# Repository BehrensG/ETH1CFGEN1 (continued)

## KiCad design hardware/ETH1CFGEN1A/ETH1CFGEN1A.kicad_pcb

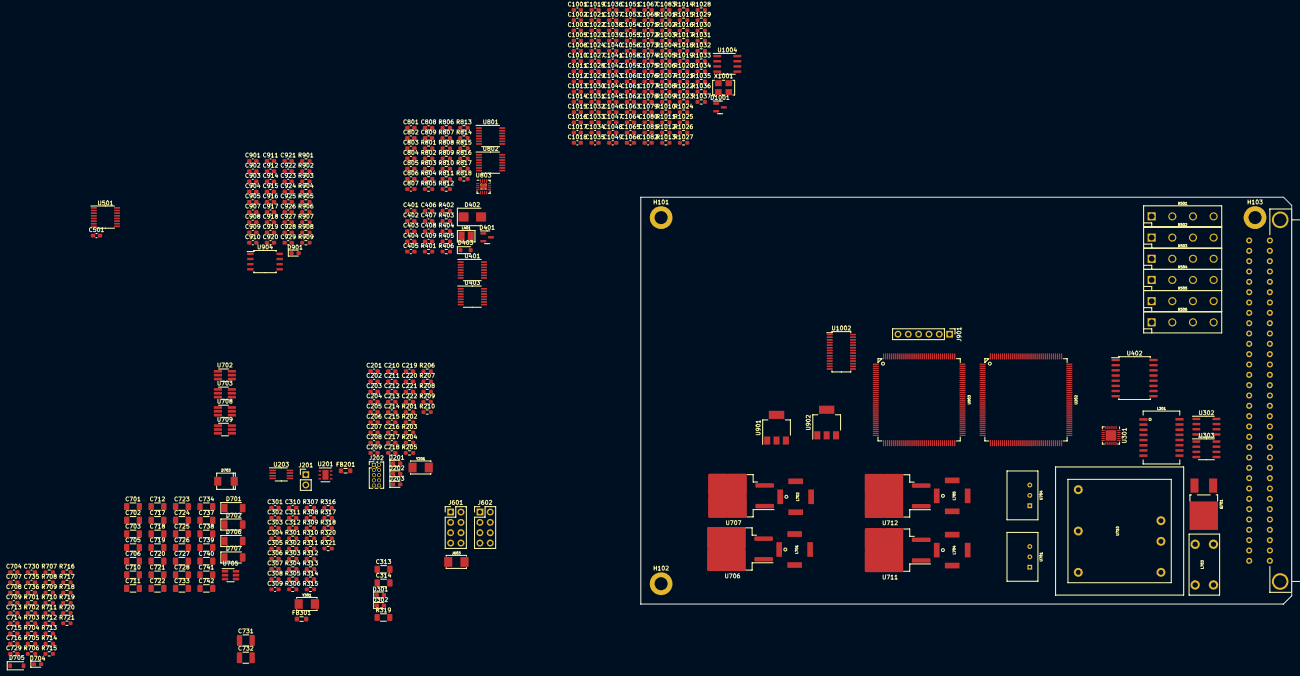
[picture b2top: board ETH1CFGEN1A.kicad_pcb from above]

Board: 4 copper layers, 160.0 x 100.0 mm, 395 parts (1 on the bottom side), 228 nets, no tracks yet.

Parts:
C201, C202, C204, C207, C209, C211, C212, C213, C214, C215, C216, C217, C218, C219, C220, C222, C302, C305, C308, C309, C310, C311, C312, C401, C403, C404, C406, C408, C707, C714, C801, C802, C803, C804, C805, C806, C808, C901, C902, C903, C904, C905, C907, C908, C909, C910, C911, C912, C914, C915, C916, C917, C918, C919, C920, C921, C922, C923, C924, C925, C926, C927, C928, C929, C1003, C1005, C1006, C1012, C1017, C1041, C1044, C1045, C1051, C1065, C1066: 100n; C_0603_1608Metric_Pad1.08x0.95mm_HandSolder
C203, C205, C301, C304: 8p; C_0603_1608Metric_Pad1.08x0.95mm_HandSolder
C206, C208: 2u2; C_0603_1608Metric_Pad1.08x0.95mm_HandSolder
C210, C221, C306, C307, C402, C405, C407, C501, C704, C708, C709, C713, C729, C730, C807, C809: 1u; C_0603_1608Metric_Pad1.08x0.95mm_HandSolder
C303: 470p; C_0603_1608Metric_Pad1.08x0.95mm_HandSolder
C313, C314: 1n/1kV; C_1206_3216Metric_Pad1.33x1.80mm_HandSolder
C409, C1067, C1068, C1080: 47p; C_0603_1608Metric_Pad1.08x0.95mm_HandSolder
C701, C710: 1u/50V; C_1206_3216Metric_Pad1.33x1.80mm_HandSolder
C702, C703, C725, C726: 10u/50V; C_1206_3216Metric_Pad1.33x1.80mm_HandSolder
C705, C706, C717, C718, C719, C720, C723, C724, C727, C728, C739: 4u7/50V; C_1206_3216Metric_Pad1.33x1.80mm_HandSolder
C711, C712, C733, C734: 1u/HC; C_1206_3216Metric_Pad1.33x1.80mm_HandSolder
C715, C716, C735, C736: 4p7; C_0603_1608Metric_Pad1.08x0.95mm_HandSolder
C721, C722: 10u/35V; C_1206_3216Metric_Pad1.33x1.80mm_HandSolder
C731, C732: 330p/2kV; C_1210_3225Metric_Pad1.33x2.70mm_HandSolder
C737, C738, C740: 4u7/25V; C_1206_3216Metric_Pad1.33x1.80mm_HandSolder
C741, C742: 10u/25V; C_1206_3216Metric_Pad1.33x1.80mm_HandSolder
C1001, C1002, C1013, C1014, C1018, C1019, C1031, C1032, C1042, C1043, C1058, C1059, C1082: 33p; C_0603_1608Metric_Pad1.08x0.95mm_HandSolder
C1010, C1011, C1061, C1062, C1075, C1077: 100p; C_0603_1608Metric_Pad1.08x0.95mm_HandSolder
C1015, C1016: 30p; C_0603_1608Metric_Pad1.08x0.95mm_HandSolder
C1021, C1022, C1027, C1028, C1033, C1034, C1055, C1056: 56p; C_0603_1608Metric_Pad1.08x0.95mm_HandSolder
C1023, C1024: 3p3; C_0603_1608Metric_Pad1.08x0.95mm_HandSolder
C1029, C1030: 120p; C_0603_1608Metric_Pad1.08x0.95mm_HandSolder
C1035, C1036, C1083: 150p; C_0603_1608Metric_Pad1.08x0.95mm_HandSolder
C1037, C1038: 62p; C_0603_1608Metric_Pad1.08x0.95mm_HandSolder
C1039, C1040: 8p2; C_0603_1608Metric_Pad1.08x0.95mm_HandSolder
C1046, C1047: 130p; C_0603_1608Metric_Pad1.08x0.95mm_HandSolder
C1048, C1049: 330p; C_0603_1608Metric_Pad1.08x0.95mm_HandSolder
C1053, C1054, C1081: 15p; C_0603_1608Metric_Pad1.08x0.95mm_HandSolder
C1060, C1071: 220n; C_0603_1608Metric_Pad1.08x0.95mm_HandSolder
C1063, C1064: 5p6; C_0603_1608Metric_Pad1.08x0.95mm_HandSolder
C1072, C1073: 22p; C_0603_1608Metric_Pad1.08x0.95mm_HandSolder
C1074, C1078, C1079: 10p; C_0603_1608Metric_Pad1.08x0.95mm_HandSolder
C1076: 1p; C_0603_1608Metric_Pad1.08x0.95mm_HandSolder
D201, D901: BLUE; LED_0603_1608Metric_Pad1.05x0.95mm_HandSolder
D202, D704: RED; LED_0603_1608Metric_Pad1.05x0.95mm_HandSolder
D203, D302: GREEN; LED_0603_1608Metric_Pad1.05x0.95mm_HandSolder
D301: YELLOW; LED_0603_1608Metric_Pad1.05x0.95mm_HandSolder
D401: BAV99; SOT-23
D402: SMBJ5.0A; D_SMB
D403: SD36C-01FTG; D_SOD-323_HandSoldering
D701, D702, D706, D707: PMEG6010EP,115; D_SOD-128
D703: SM6T30AY; DO_214AA_REV
D705: MMSZ5249B; D_SOD-123
D1001: BAS40-04; SOT-23
F701: MF-LSMF185/33X; Fuse_SMD2920
FB201, FB301: 742792031; L_0805_2012Metric_Pad1.05x1.20mm_HandSolder
H101, H102, H103: MountingHole; MountingHole_3.2mm_M3_DIN965_Pad
J201: Conn_02x01; PinHeader_1x02_P2.54mm_Vertical
J202: 20021111-00010T4LF; PinHeader_2x05_P1.27mm_Vertical
J501: C64AC; Socket_DIN41612-CaseC1-AC-Male-64Pin-2rows
J601, J602: Conn_02x04_Odd_Even; PinHeader_2x04_P2.54mm_Vertical
J603: Conn_Coaxial; NX5032GA
J901: Conn_01x06; PinHeader_1x06_P2.54mm_Vertical
K501, K502, K503, K504, K505, K506: HE3621A0510; HE360_x-5050462-8
L301: 749010012A
L401: CW252016-R33G; CW252016
L701, L702, L704, L705: 74489440068
L703: 7448014501
Q701: IRFR5410; TO-252-2_Rectifier
R201, R205: 680; R_0603_1608Metric_Pad0.98x0.95mm_HandSolder
R202, R209, R210, R303, R306, R307, R308, R309, R311, R401, R901, R902, R909, R1002, R1017, R1023, R1027: 10k; R_0603_1608Metric_Pad0.98x0.95mm_HandSolder
R203: 560; R_0603_1608Metric_Pad0.98x0.95mm_HandSolder
R204, R206, R207, R208, R817, R818, R904, R908: 4k7; R_0603_1608Metric_Pad0.98x0.95mm_HandSolder
R301, R302, R304, R305: 33; R_0603_1608Metric_Pad0.98x0.95mm_HandSolder
R310: 1k5; R_0603_1608Metric_Pad0.98x0.95mm_HandSolder
R312: 12k1; R_0603_1608Metric_Pad0.98x0.95mm_HandSolder
R313, R314: 270; R_0603_1608Metric_Pad0.98x0.95mm_HandSolder
R315, R316, R317, R318: 49R9; R_0603_1608Metric_Pad0.98x0.95mm_HandSolder
R319: 1M/1kV; R_1206_3216Metric_Pad1.30x1.75mm_HandSolder
R320, R321: 75/1%; R_0603_1608Metric_Pad0.98x0.95mm_HandSolder
R402: 14k7; R_0603_1608Metric_Pad0.98x0.95mm_HandSolder
R403, R1005, R1015, R1016, R1019, R1022, R1025: 100; R_0603_1608Metric_Pad0.98x0.95mm_HandSolder
R404, R809, R810, R811, R812, R905, R1001, R1007, R1014: 1k; R_0603_1608Metric_Pad0.98x0.95mm_HandSolder
R405: 47; R_0603_1608Metric_Pad0.98x0.95mm_HandSolder
R406, R1003, R1004, R1028, R1035: 51R1; R_0603_1608Metric_Pad0.98x0.95mm_HandSolder
R701, R703, R706, R708, R712, R714, R718, R720: 1M; R_0603_1608Metric_Pad0.98x0.95mm_HandSolder
R702, R704, R713, R715: 287k; R_0603_1608Metric_Pad0.98x0.95mm_HandSolder
R705, R1031, R1034: 100k; R_0603_1608Metric_Pad0.98x0.95mm_HandSolder
R707: 97k6; R_0603_1608Metric_Pad0.98x0.95mm_HandSolder
R709: 46k4; R_0603_1608Metric_Pad0.98x0.95mm_HandSolder
R710: 6k8; R_0603_1608Metric_Pad0.98x0.95mm_HandSolder
R711: 370; R_0603_1608Metric_Pad0.98x0.95mm_HandSolder
R716, R717: OPT; R_0603_1608Metric_Pad0.98x0.95mm_HandSolder
R719, R802, R806: 249k; R_0603_1608Metric_Pad0.98x0.95mm_HandSolder
R721: 111k; R_0603_1608Metric_Pad0.98x0.95mm_HandSolder
R801, R805, R813: 33k; R_0603_1608Metric_Pad0.98x0.95mm_HandSolder
R803, R804, R807, R808, R814: 49k9; R_0603_1608Metric_Pad0.98x0.95mm_HandSolder
R815: 0; R_0603_1608Metric_Pad0.98x0.95mm_HandSolder
R816: DNP; R_0603_1608Metric_Pad0.98x0.95mm_HandSolder
R903: 2k2; R_0603_1608Metric_Pad0.98x0.95mm_HandSolder
R906: 27; R_0603_1608Metric_Pad0.98x0.95mm_HandSolder
R907: 1K; R_0603_1608Metric_Pad0.98x0.95mm_HandSolder
R1006: 82k5; R_0603_1608Metric_Pad0.98x0.95mm_HandSolder
R1008: 2k; R_0603_1608Metric_Pad0.98x0.95mm_HandSolder
R1009, R1013: 69; R_0603_1608Metric_Pad0.98x0.95mm_HandSolder
R1010, R1011: 261; R_0603_1608Metric_Pad0.98x0.95mm_HandSolder
R1012: 21k5; R_0603_1608Metric_Pad0.98x0.95mm_HandSolder
R1018, R1026: 1k78; R_0603_1608Metric_Pad0.98x0.95mm_HandSolder
R1020, R1021: 511; R_0603_1608Metric_Pad0.98x0.95mm_HandSolder
R1024: 21R5; R_0603_1608Metric_Pad0.98x0.95mm_HandSolder
R1029, R1030: 200; R_0603_1608Metric_Pad0.98x0.95mm_HandSolder
R1032, R1033: 953; R_0603_1608Metric_Pad0.98x0.95mm_HandSolder
R1036: 34R8; R_0603_1608Metric_Pad0.98x0.95mm_HandSolder
R1037: 196; R_0603_1608Metric_Pad0.98x0.95mm_HandSolder
U201: HDC1080; Texas_PWSON-N6
U202: STM32F746ZG; TQFP-144_20x20mm_P0.5mm
U203: 24LC08B-E/MS; MSOP-8_3x3mm_P0.65mm
U301: LAN8742; QFN-24-1EP_4x4mm_P0.5mm_EP2.6x2.6mm
U302, U303: LC03-3.3BTG; SOIC-8_3.9x4.9mm_P1.27mm
U401: TXB0104PW; TSSOP-14_4.4x5mm_P0.65mm
U402: ADuM5402; SOIC-16W_7.5x10.3mm_P1.27mm
U403: 74AC125; TSSOP-14_4.4x5mm_P0.65mm
U501: ULN2003AIPWR; TSSOP-16_4.4x5mm_P0.65mm
U701: TSR1-2450; TSR1
U702, U703, U708, U709: LT8330ES6#TRMPBF; TSOT-23-6_HandSoldering
U704: TSR1-2433; TSR1
U705: MAX5902AAEUT+T; SOT-23-6_Handsoldering
U706: MC7815BD2TR4G; TO-263-2
U707: MC7915ACD2TG; TO-263-2
U710: THL15-2415WI; THL15
U711: MC7805CD2TG; TO-263-2
U712: L7905CD2T-TR; TO-263-2
U801, U802: TL074HIPWR; TSSOP-14_4.4x5mm_P0.65mm
U803: TLA2528IRTER; WQFN-16-1EP_3x3mm_P0.5mm_EP1.6x1.6mm_ThermalVias
U901: TLV1117LV33DCYR; SOT-223-3_TabPin2
U902: TLV1117LV12DCYR; SOT-223-3_TabPin2
U903: XC6SLX9-3TQG144I; TQFP-144_20x20mm_P0.5mm
U904: W25Q64JV; SOIC-8_5.23x5.23mm_P1.27mm
U1002: AD9744; TSSOP-28_4.4x9.7mm_P0.65mm
U1004: THS3001CD; SOIC-8_3.9x4.9mm_P1.27mm
X1001: SG5032CAN 50.000000M-TJGA3; Oscillator_SMD_SeikoEpson_SG8002LB-4Pin_5.0x3.2mm
Y201: NX5032GA-16.000M; NX5032GA
Y301: NX5032GA-25.000000MHZ-LN-CD-1; NX5032GA

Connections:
+3.3V: C201.1, C202.1, C204.1, C207.1, C209.1, C210.1, C211.1, C212.1, C213.1, C214.1, C215.1, C216.1, C217.1, C218.1, C219.1, C220.1, C302.1, C305.1, C401.1, C402.1, C713.1, C714.1, C808.2, D201.2 (A), D202.2 (A), D203.2 (A), FB201.2, FB301.2, J202.1, J602.1, R202.2, R204.1, R206.1, R207.1, R208.1, R210.1, R306.1, R307.1, R308.1, R309.1, R310.1, R401.1, R817.1, R818.1, R1001.1, U201.5 (VCC), U202.6 (VBAT), U202.17 (VDD), U202.30 (VDD), U202.39 (VDD), U202.52 (VDD), U202.62 (VDD), U202.72 (VDD), U202.84 (VDD), U202.95 (VDDUSB), U202.108 (VDD), U202.121 (VDD), U202.131 (VDD), U202.143 (PDR_ON), U202.144 (VDD), U203.8 (VCC), U301.9 (VDDIO), U401.1 (VCCA), U704.3 (VO), U802.3 (+), U803.10 (DVDD), X1001.4 (VCC)
+3V3_WFD1: C1005.1, D1001.2, U1002.16 (REFLO), U1002.24 (AVDD)
+3V3_WFD2: C1003.1, R1007.2, U1002.27 (DVDD)
+5V: C403.1, C404.1, C405.1, C741.1, C807.2, J602.3, R805.2, U401.14 (VCCB), U402.1 (VDD1), U711.3 (OUT), U803.7 (AVDD)
+5VD: C501.1, C704.1, C707.1, C903.1, J602.2, K501.2, K502.2, K503.2, K504.2, K505.2, K506.2, R813.2, U501.9 (COM), U701.3 (VO), U901.3 (VI)
+5VP: C406.1, C407.1, C408.1, R404.1, U402.10 (VSEL), U402.16 (VISO), U403.14 (VCC)
+15V: C721.1, C801.2, C803.2, C805.2, J602.7, R806.2, U706.3 (OUT), U801.4 (V+), U802.4 (V+)
+15V_WFD1: C1017.1, R1012.2
+15V_WFD2: C1012.1, U1004.7 (V+)
+24V: F701.2, J501.A31 (31A), J501.A32 (32A), J501.C31 (31C), J501.C32 (32C)
-5V: C742.1, J602.4, R801.2, U712.3 (VO)
-15V: C722.1, C802.2, C804.2, C806.2, J602.8, R802.2, U707.3 (VO), U801.11 (V-), U802.11 (V-)
-15V_WFD2: C1041.1, U1004.4 (V-)
/Connector/A: J501.A2 (2A), J501.C2 (2C), K501.4
/Connector/B: J501.A3 (3A), J501.C3 (3C), K502.4
/Connector/C: J501.A4 (4A), J501.C4 (4C), K503.4
/Connector/CXN_REL1: U202.70 (PB11,TIM2_CH4,I2C2_SDA,DFSDM1_CKIN7,USA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), U501.1 (I1)
/Connector/CXN_REL2: U202.69 (PB10,TIM2_CH3,I2C2_SCL,SPI2_SCK,I2S2_CK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), U501.2 (I2)
/Connector/CXN_REL3: U202.68 (PE15,TIM1_BKIN,FMC_D12,LCD_R7,EVENTOUT), U501.3 (I3)
/Connector/CXN_REL4: U202.67 (PE14,TIM1_CH4,SPI4_MOSI,SAI2_MCLK_B,FMC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), U501.4 (I4)
/Connector/CXN_REL5: U202.66 (PE13,TIM1_CH3,SPI4_MISO,DFSDM1_CKIN5,SA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), U501.5 (I5)
/Connector/CXN_REL6: U202.65 (PE12,TIM1_CH3N,SPI4_SCK,DFSDM1_DATIN5,S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), U501.6 (I6)
/Connector/D: J501.A5 (5A), J501.C5 (5C), K504.4
/Connector/E: J501.A6 (6A), J501.C6 (6C), K505.4
/Connector/EXT_TRIG: C409.1, D403.1 (A1), J501.A16 (16A), L401.1
/Connector/F: J501.A7 (7A), J501.C7 (7C), K506.4
/Connector/RX+: J501.A20 (20A), U303.8
/Connector/RX-: J501.A21 (21A), U303.5
/Connector/SIGNAL: J603.1 (In), K501.1, K502.1
/Connector/TX+: J501.C20 (20C), U302.8
/Connector/TX-: J501.C21 (21C), U302.5
/Ethernet/ETH_RXN: L301.8 (RD-), R318.2, U301.22 (RXN)
/Ethernet/ETH_RXP: L301.6 (RD+), R317.2, U301.23 (RXP)
/Ethernet/ETH_TXN: L301.3 (TD-), R316.2, U301.20 (TXN)
/Ethernet/ETH_TXP: L301.1 (TD+), R315.2, U301.21 (TXP)
/Ethernet/MDIO: R310.2, U202.36 (PA2,TIM2_CH3,TIM5_CH3,TIM9_CH1,USART2_T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), U301.12 (MDIO)
/Ethernet/MODE0: R301.1, R306.2, U301.8 (RXD0/MODE0)
/Ethernet/MODE1: R302.1, R307.2, U301.7 (RXD1/MODE1)
/Ethernet/MODE2: R304.1, R308.2, U301.11 (CRS_DV/MODE2)
/Ethernet/REFCLK0: R305.1, R309.2, U301.14 (~INT/REFCLK0)
/Ethernet/REF_CLK: R305.2, U202.35 (PA1,TIM2_CH2,TIM5_CH2,UART2_RTS,UART4_R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)
/Ethernet/RMII_CRS_DV: R304.2, U202.43 (PA7,TIM1_CH1N,TIM3_CH2,TIM8_CH1N,SPI1_M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)
/Ethernet/RMII_MDC: U202.27 (PC1,TRACED0,_DFSDM1_DATIN0,SPI2_MOSI,I2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), U301.13 (MDC)
/Ethernet/RMII_RXD0: R301.2, U202.44 (PC4,DFSDM1_CKIN2,I2S1_MCK,SPDIF_RX2,ETH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)
/Ethernet/RMII_RXD1: R302.2, U202.45 (PC5,DFSDM1_DATIN2,SPDIF_RX3,ETH_MII_RXD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)
/Ethernet/RMII_TXD0: U202.128 (PG13,TRACED0,LPTIM1_OUT,SPI6_SCK,USART6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), U301.17 (TXD0)
/Ethernet/RMII_TXD1: U202.129 (PG14,TRACED1,LPTIM1_ETR,SPI6_MOSI,USART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), U301.18 (TXD1)
/Ethernet/RMII_TXEN: U202.126 (PG11,SPI1_SCK,I2S1_CK,SPDIF_RX0,SDMMC2_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), U301.16 (TXEN)
/FPGA/CMPCS_B_2: R909.1, U903.72 (CMPCS_B_2)
/FPGA/DONE_2: R907.1, U903.71 (DONE_2)
/FPGA/FLASH_HOLD: R901.2, U904.7 (IO3)
/FPGA/FLASH_INIT_B: R904.2, U903.39 (IO_L65P_INIT_B_2)
/FPGA/FLASH_SCK: U903.70 (IO_L1P_CCLK_2), U904.6 (CLK)
/FPGA/FLASH_WP: R902.2, U904.3 (IO2)
/FPGA/FLASH_nCS: R903.2, U903.38 (IO_L65N_CSO_B_2), U904.1 (~CS)
/FPGA/FPGA_TCK: J901.3, U903.109 (TCK)
/FPGA/FPGA_TDI: J901.5, U903.110 (TDI)
/FPGA/FPGA_TDO: J901.4, U903.106 (TDO)
/FPGA/FPGA_TMS: J901.2, U903.107 (TMS)
/FPGA/PROG_B_2: R908.1, U903.37 (PROGRAM_B_2)
/MCU/EEPROM_SCL: R208.2, R817.2, U202.81 (PD12,TIM4_CH1,LPTIM1_IN1,I2C4_SCL,USART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), U203.6 (SCL), U803.13 (SCL)
/MCU/EEPROM_SDA: R207.2, R818.2, U202.82 (PD13,TIM4_CH2,LPTIM1_OUT,I2C4_SDA,QUADS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), U203.5 (SDA), U803.14 (SDA)
/MCU/EEPROM_WP: U202.89 (PG4,FMC_A14,FMC_BA0,EVENTOUT), U203.7 (WP)
/MCU/GPIO1: J601.5, U202.133 (PB3,JTDO,TRACESWO,TIM2_CH2,SPI1_SCK,I2S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)
/MCU/GPIO2: J601.7, U202.134 (PB4,NJTRST,TIM3_CH1,SPI1_MISO,SPI3_MISO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)
/MCU/LED_BLUE: R201.1, U202.48 (PB2,SAI1_SD_A,SPI3_MOSI,I2S3_SD,QUADSPI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)
/MCU/LED_GREEN: R205.1, U202.50 (PF12,FMC_A6,EVENTOUT)
/MCU/LED_RED: R203.1, U202.49 (PF11,SPI5_MOSI,SAI2_SD_B,FMC_SDNRAS,_DC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)
/MCU/MCU_DEFAULT: J201.1, R202.1, U202.63 (PE10,TIM1_CH2N,DFSDM1_DATIN4,UART7_CTS,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)
/MCU/MCU_VDDA: C221.1, FB201.1, U202.32 (VREF+), U202.33 (VDDA)
/MCU/NRST: C222.1, J202.10, R210.2, U202.25 (NRST), U301.15 (~RST)
/MCU/SENS_SCL: R204.2, U201.6 (SCL)
/MCU/SENS_SDA: R206.2, U201.1 (SDA)
/MCU/SPI1_CLK: J601.6, U202.41 (PA5,TIM2_CH1,TIM2_ETR,TIM8_CH1N,SPI1_SC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)
/MCU/SPI1_CS: J601.8, U202.40 (PA4,SPI1_NSS,I2S1_WS,SPI3_NSS,I2S3_WS,U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)
/MCU/SPI1_MISO: J601.4, U202.42 (PA6,TIM1_BKIN,TIM3_CH1,TIM8_BKIN,SPI1_M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)
/MCU/SPI1_MOSI: J601.2, U202.135 (PB5,UART5_RX,TIM3_CH2,I2C1_SMBA,SPI1_MO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)
/MCU/TCK_SWCLK: J202.4, U202.109 (PA14,JTCK-SWCLK,EVENTOUT)
/MCU/TMS_SWDIO: J202.2, U202.105 (PA13,JTMS-SWDIO,EVENTOUT)
/MCU/TRIG_EN: U202.76 (PB15,RTC_REFIN,TIM1_CH3N,TIM8_CH3N,USAR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), U401.2 (A1)
/MCU/TRIG_IN: U202.74 (PB13,TIM1_CH1N,SPI2_SCK,I2S2_CK,DFSDM1_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), U401.4 (A3)
/MCU/TRIG_OUT: U202.75 (PB14,TIM1_CH2N,TIM8_CH2N,USART1_TX,SPI2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), U401.3 (A2)
/Self test/AIN0: U802.1, U802.2 (-), U803.15 (AIN0/GPIO0)
/Self test/AIN1: U802.6 (-), U802.7, U803.16 (AIN1/GPIO1)
/Self test/AIN2: R811.1, U801.1, U803.1 (AIN2/GPIO2)
/Self test/AIN3: U802.8, U802.9 (-), U803.2 (AIN3/GPIO3)
/Self test/AIN4: U802.13 (-), U802.14, U803.3 (AIN4/GPIO4)
/Self test/AIN5: R812.1, U801.8, U803.4 (AIN5/GPIO5)
/Trigger/EXT_TRIG_SIGN: R402.1, U402.12 (VIC), U403.3 (O)
/Trigger/TRIG_OUT_EN: U402.14 (VOA), U403.4 (EN), U403.10 (EN), U403.13 (EN)
/Trigger/TRIG_OUT_SIGN: U402.13 (VOB), U403.5 (D), U403.9 (D), U403.12 (D)
/Waveform DAC/V_AMPL: D1001.3, R1002.1, U1002.17 (REFIO)
/Waveform DAC/V_DTY_CYCL: C1044.1, C1051.1, R1014.1
/Waveform DAC/WFDAC_CLK: R1003.2, U1002.28 (CLK)
Earth: C313.1, C314.2, J501.A18 (18A), J501.A22 (22A), J501.C18 (18C), J501.C22 (22C), R319.1
FPGA_1V2: C915.1, C923.1, C924.1, C925.1, C926.1, C927.1, U902.2 (VO), U903.19 (VCCINT), U903.28 (VCCINT), U903.52 (VCCINT), U903.89 (VCCINT), U903.128 (VCCINT)
FPGA_3V3: C901.1, C902.1, C904.1, C905.1, C907.1, C908.1, C909.1, C910.1, C911.1, C912.1, C914.1, C916.1, C917.1, C918.1, C919.1, C920.1, C921.1, C922.1, C928.1, C929.1, D901.2 (A), J901.1, R901.1, R902.1, R903.1, R904.1, R905.1, R908.2, R909.2, U901.2 (VO), U902.3 (VI), U903.4 (VCCO_3), U903.18 (VCCO_3), U903.20 (VCCAUX), U903.31 (VCCO_3), U903.36 (VCCAUX), U903.42 (VCCO_2), U903.53 (VCCAUX), U903.63 (VCCO_2), U903.69 (IO_L1N_M0_CMPMISO_2), U903.76 (VCCO_1), U903.86 (VCCO_1), U903.90 (VCCAUX), U903.103 (VCCO_1), U903.122 (VCCO_0), U903.125 (VCCO_0), U903.129 (VCCAUX), U903.135 (VCCO_0), U904.8 (VCC)
GND1: C406.2, C407.2, C408.2, D401.1 (K), D402.2 (A), D403.2 (A2), J501.C16 (16C), R406.2, U402.9 (GNDISO), U402.15 (GNDISO), U403.1 (EN), U403.7 (GND)
GNDA: C201.2, C202.2, C203.2, C204.2, C205.2, C206.2, C207.2, C208.2, C209.2, C210.2, C211.2, C212.2, C213.2, C214.2, C215.2, C216.2, C217.2, C218.2, C219.2, C220.2, C221.2, C222.2, C301.2, C302.2, C303.2, C304.2, C305.2, C306.2, C307.2, C308.2, C309.2, C310.2, C311.2, C312.2, C313.2, C401.2, C402.2, C403.2, C404.2, C405.2, C501.2, C701.2, C702.2, C703.2, C704.2, C705.2, C706.2, C707.2, C708.2, C709.2, C710.2, C713.2, C714.2, C717.2, C718.2, C719.2, C720.2, C721.2, C722.2, C725.2, C726.2, C727.2, C728.2, C729.2, C730.2, C732.1, C737.2, C738.2, C739.2, C740.2, C741.2, C742.2, C801.1, C802.1, C803.1, C804.1, C805.1, C806.1, C807.1, C808.1, C809.1, C901.2, C902.2, C903.2, C904.2, C905.2, C907.2, C908.2, C909.2, C910.2, C911.2, C912.2, C914.2, C915.2, C916.2, C917.2, C918.2, C919.2, C920.2, C921.2, C922.2, C923.2, C924.2, C925.2, C926.2, C927.2, C928.2, C929.2, C1001.2, C1002.2, C1003.2, C1005.2, C1006.2, C1010.2, C1011.1, C1012.2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
GNDPWR: C723.2, C724.2, D703.2 (A), D704.1 (K), J501.A27 (27A), J501.A28 (28A), J501.C27 (27C), J501.C28 (28C), L703.1, U705.4 (GND)
unnamed: C314.1, R320.2, R321.2
unnamed: C409.2, R406.1
unnamed: C1006.1, R1009.2, R1010.1, R1013.2
unnamed: R1010.2, R1011.1
unnamed: C1013.1, C1018.1
unnamed: C1014.2, C1019.1
unnamed: C1015.1, C1023.1
unnamed: C1016.2, C1024.2
unnamed: C1018.2, C1021.1, C1027.1, C1031.1
unnamed: C1019.2, C1022.2, C1028.2, C1032.1
unnamed: C1031.2, C1033.1, C1037.1, C1042.1
unnamed: C1032.2, C1034.2, C1038.2, C1043.1
unnamed: C1035.1, C1039.1
unnamed: C1036.2, C1040.2
unnamed: C1042.2, C1046.1, C1053.1, C1058.1
unnamed: C1043.2, C1047.2, C1054.2, C1059.1
unnamed: C1048.1, C1055.1, R1015.1, R1018.1
unnamed: C1049.2, C1056.2, R1016.2, R1018.2
unnamed: C1051.2, R1023.2, R1024.1
unnamed: C1058.2, C1061.1, C1063.1, R1019.1, R1026.1
unnamed: C1059.2, C1062.2, C1064.2, R1022.2, R1026.2
unnamed: C1067.1, C1072.1, R1019.2, R1020.1
unnamed: C1068.2, C1073.2, R1021.2, R1022.1
unnamed: C1071.1, R1024.2, R1025.1
unnamed: C1078.2, R1029.1
unnamed: C1079.1, R1030.1
unnamed: C1081.1, R1037.2
unnamed: C1082.1, R1036.2
unnamed: D201.1 (K), R201.2
unnamed: D202.1 (K), R203.2
unnamed: D203.1 (K), R205.2
unnamed: D301.2 (A), R311.1, U301.2 (LED2/~INTSEL)
unnamed: D301.1 (K), R313.1
unnamed: D302.2 (A), U301.3 (LED1/REGOFF)
unnamed: D302.1 (K), R314.1
unnamed: D401.2 (A), D402.1 (K), R404.2
unnamed: C712.1, D701.2 (A), L702.2
unnamed: C711.1, D702.2 (A), L701.2
unnamed: C715.1, C717.1, C719.1, D702.1 (K), R706.1, U706.1 (IN)
unnamed: D703.1 (K), F701.1, Q701.3 (S), R705.1, U705.1 (VS)
unnamed: D704.2 (A), R710.2, R711.2
unnamed: D705.2 (A), R711.1
unnamed: C723.1, C724.1, D705.1 (K), L703.2, Q701.2 (D), R710.1, U705.2 (DRAIN)
unnamed: C734.1, D706.2 (A), L705.2
unnamed: C733.1, D707.2 (A), L704.2
unnamed: C735.1, C737.1, C739.1, D707.1 (K), R718.1, U711.1 (IN)
unnamed: D901.1 (K), R907.2
unnamed: L301.10 (CRX), R320.1
unnamed: L301.15 (CTX), R321.1
unnamed: L301.11 (RX+), U303.1
unnamed: L301.9 (RX-), U303.4
unnamed: L301.16 (TX+), U302.1
unnamed: L301.14 (TX-), U302.4
unnamed: L401.2, R405.2
unnamed: Q701.1 (G), U705.3 (GATE)
unnamed: R1006.2, R1011.2, R1012.1
unnamed: R1033.2, R1034.2, R1036.1, R1037.1, U1004.6
unnamed: R209.1, U202.138 (BOOT0)
unnamed: C203.1, U202.23 (PH0,EVENTOUT,OSC_IN), Y201.1
unnamed: C205.1, U202.24 (PH1,EVENTOUT,OSC_OUT), Y201.2
unnamed: C206.1, U202.71 (VCAP_1)
unnamed: C208.1, U202.106 (VCAP_2)
unnamed: R312.2, U301.24 (RBIAS)
unnamed: R303.1, U301.10 (RXER/PHYAD0)
unnamed: C303.1, C306.1, U301.6 (VDDCR)
unnamed: C301.1, U301.5 (XTAL1/CLKIN), Y301.2
unnamed: C304.1, U301.4 (XTAL2), Y301.1
unnamed: U401.13 (B1), U402.3 (VIA)
unnamed: U401.12 (B2), U402.4 (VIB)
unnamed: U401.11 (B3), U402.5 (VOC)
unnamed: R401.2, U401.8 (OE)
unnamed: R402.2, R403.1, U403.2 (D)
unnamed: D401.3 (K), R403.2, R405.1, U403.6 (O), U403.8 (O), U403.11 (O)
unnamed: K506.3, U501.16 (O1)
unnamed: K505.3, U501.15 (O2)
unnamed: K504.3, U501.14 (O3)
unnamed: K503.3, U501.13 (O4)
unnamed: K502.3, U501.12 (O5)
unnamed: K501.3, U501.11 (O6)
unnamed: R701.2, R702.1, U702.4 (EN/UVLO)
unnamed: C715.2, R706.2, R707.1, U702.3 (FBX)
unnamed: C708.1, U702.5 (INTVCC)
unnamed: C711.2, L701.4, U702.1 (SW)
unnamed: R703.2, R704.1, U703.4 (EN/UVLO)
unnamed: C716.2, R708.2, R709.1, U703.3 (FBX)
unnamed: C709.1, U703.5 (INTVCC)
unnamed: C712.2, L702.4, U703.1 (SW)
unnamed: R705.2, U705.6 (ON/~OFF)
unnamed: C716.1, C718.1, C720.1, L702.3, R708.1, U707.2 (VI)
unnamed: R712.2, R713.1, U708.4 (EN/UVLO)
unnamed: C735.2, R718.2, R719.1, U708.3 (FBX)
unnamed: C729.1, U708.5 (INTVCC)
unnamed: C733.2, L704.4, U708.1 (SW)
unnamed: R714.2, R715.1, U709.4 (EN/UVLO)
unnamed: C736.2, R720.2, R721.1, U709.3 (FBX)
unnamed: C730.1, U709.5 (INTVCC)
unnamed: C734.2, L705.4, U709.1 (SW)
unnamed: C731.2, L703.3, U710.1 (+VIN)
unnamed: C732.2, L703.4, U710.2 (-VIN)
unnamed: R716.2, R717.1, U710.4 (TRIM)
unnamed: C736.1, C738.1, C740.1, L705.3, R720.1, U712.2 (VI)
unnamed: R809.1, R811.2, U801.2 (-)
unnamed: R801.1, R803.1, U801.5 (+)
unnamed: R809.2, U801.6 (-), U801.7
unnamed: R810.1, R812.2, U801.9 (-)
unnamed: R802.1, R804.1, U801.12 (+)
unnamed: R810.2, U801.13 (-), U801.14
unnamed: R805.1, R807.1, U802.5 (+)
unnamed: R813.1, R814.1, U802.10 (+)
unnamed: R806.1, R808.1, U802.12 (+)
unnamed: R815.2, R816.2, U803.11 (ADDR)
unnamed: C809.2, R815.1, U803.8 (DECAP)
unnamed: C1060.1, R1014.2
unnamed: R1017.2, R1023.1
unnamed: R1002.2, R1006.1
unnamed: R1008.2, U1002.18 (FS_ADJ)
unnamed: C1002.1, R1009.1, U1002.22 (IOUTA)
unnamed: C1001.1, R1013.1, U1002.21 (IOUTB)
unnamed: R1007.1, U1002.25 (MODE)
unnamed: C1074.1, C1080.1
unnamed: C1074.2, C1076.1, R1025.2, R1027.1
unnamed: C1076.2, R1027.2, R1028.1, R1028.2
unnamed: R1029.2, R1031.2, R1032.1, U1004.3 (+)
unnamed: R1030.2, R1033.1, R1034.1, U1004.2 (-)
unnamed: R1003.1, R1004.1, X1001.3 (OUT)
unnamed: R1001.2, X1001.1 (~ST)
VCCQ: C307.1, C308.1, C309.1, C310.1, C311.1, C312.1, FB301.1, L301.2 (CTD), L301.7 (CRD), R315.1, R316.1, R317.1, R318.1, U301.1 (VDD2A), U301.19 (VDD1A)
VPP: C701.1, C702.1, C703.1, C705.1, C706.1, C710.1, C725.1, C726.1, C727.1, C728.1, C731.1, L701.1, L702.1, L704.1, L705.1, R701.1, R703.1, R712.1, R714.1, R716.1, U701.1 (VI), U702.6 (VIN), U703.6 (VIN), U704.1 (VI), U708.6 (VIN), U709.6 (VIN), U710.3 (+VOUT)

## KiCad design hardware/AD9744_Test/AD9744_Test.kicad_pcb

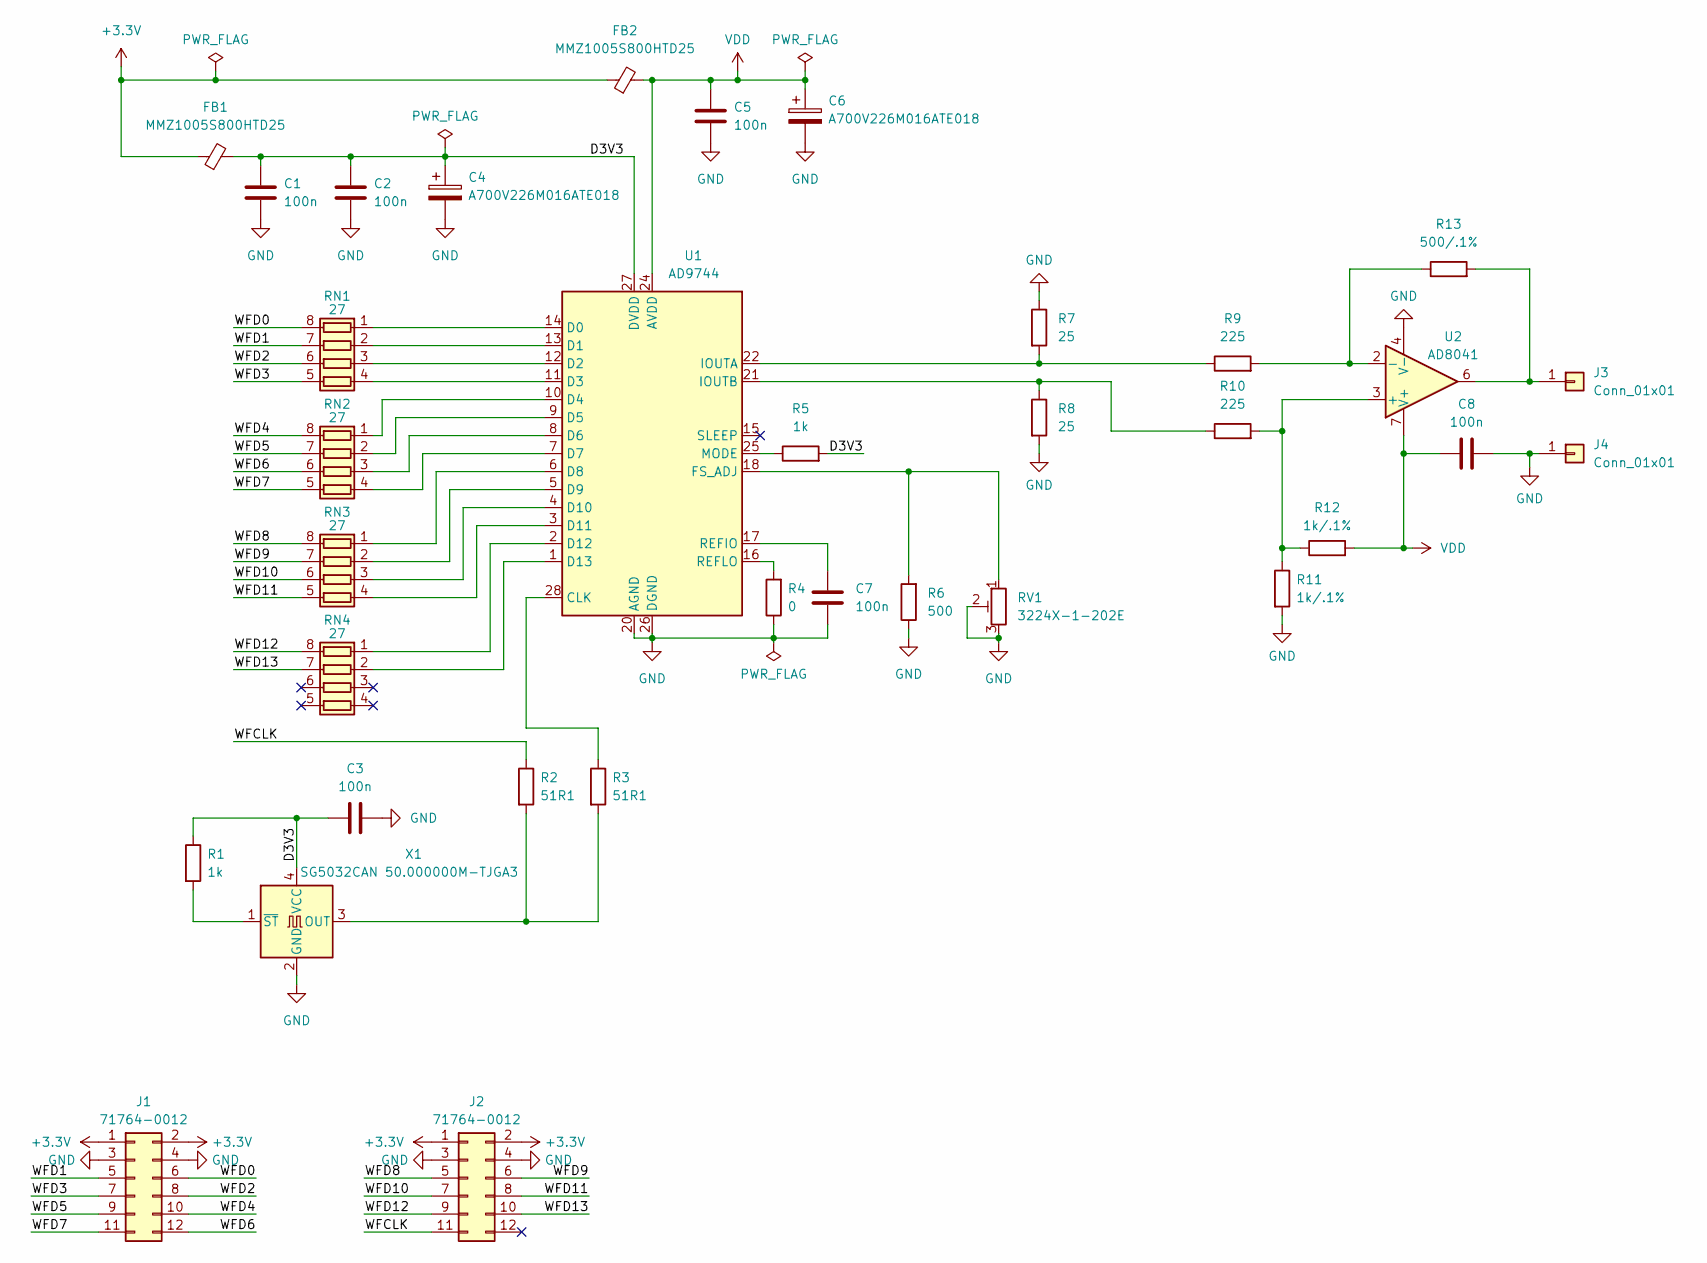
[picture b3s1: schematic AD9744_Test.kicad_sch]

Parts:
C1, C2, C3, C5, C7, C8: 100n; C_0603_1608Metric_Pad1.08x0.95mm_HandSolder
C4, C6: A700V226M016ATE018; CP_EIA-7343-20_Kemet-V_Pad2.25x2.55mm_HandSolder
FB1, FB2: MMZ1005S800HTD25; L_0805_2012Metric_Pad1.15x1.40mm_HandSolder
J1, J2: 71764-0012; PinHeader_2x06_P2.54mm_Horizontal
J3, J4: Conn_01x01; PinHeader_1x01_P2.54mm_Vertical
R1, R5: 1k; R_0603_1608Metric_Pad0.98x0.95mm_HandSolder
R2, R3: 51R1; R_0603_1608Metric_Pad0.98x0.95mm_HandSolder
R4: 0; R_0603_1608Metric_Pad0.98x0.95mm_HandSolder
R6: 500; R_0603_1608Metric_Pad0.98x0.95mm_HandSolder
R7, R8: 25; R_0603_1608Metric_Pad0.98x0.95mm_HandSolder
R9, R10: 225; R_0603_1608Metric_Pad0.98x0.95mm_HandSolder
R11, R12: 1k/.1%; R_0603_1608Metric_Pad0.98x0.95mm_HandSolder
R13: 500/.1%; R_0603_1608Metric_Pad0.98x0.95mm_HandSolder
RN1, RN2, RN3, RN4: 27; R_Array_Concave_4x0603
RV1: 3224X-1-202E; Potentiometer_Bourns_3224X_Vertical
U1: AD9744; TSSOP-28_4.4x9.7mm_P0.65mm
U2: AD8041; SOIC-8_3.9x4.9mm_P1.27mm
X1: SG5032CAN 50.000000M-TJGA3; Oscillator_SMD_SeikoEpson_SG8002LB-4Pin_5.0x3.2mm

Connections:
+3.3V: FB1.1, FB2.1, J1.1, J1.2, J2.1, J2.2
/D3V3: C1.1, C2.1, C3.1, C4.1, FB1.2, R1.1, R5.2, U1.27 (DVDD), X1.4 (VCC)
/WFCLK: J2.11, R2.1
/WFD0: J1.6, RN1.8 (R1.2)
/WFD1: J1.5, RN1.7 (R2.2)
/WFD2: J1.8, RN1.6 (R3.2)
/WFD3: J1.7, RN1.5 (R4.2)
/WFD4: J1.10, RN2.8 (R1.2)
/WFD5: J1.9, RN2.7 (R2.2)
/WFD6: J1.12, RN2.6 (R3.2)
/WFD7: J1.11, RN2.5 (R4.2)
/WFD8: J2.5, RN3.8 (R1.2)
/WFD9: J2.6, RN3.7 (R2.2)
/WFD10: J2.7, RN3.6 (R3.2)
/WFD11: J2.8, RN3.5 (R4.2)
/WFD12: J2.9, RN4.8 (R1.2)
/WFD13: J2.10, RN4.7 (R2.2)
GND: C1.2, C2.2, C3.2, C4.2, C5.2, C6.2, C7.2, C8.2, J1.3, J1.4, J2.3, J2.4, J4.1, R4.1, R6.1, R7.1, R8.2, R11.2, RV1.2, RV1.3, U1.20 (AGND), U1.26 (DGND), U2.4 (V-), X1.2 (GND)
unnamed: J3.1, R13.2, U2.6
unnamed: RN1.1 (R1.1), U1.14 (D0)
unnamed: RN1.2 (R2.1), U1.13 (D1)
unnamed: RN1.3 (R3.1), U1.12 (D2)
unnamed: RN1.4 (R4.1), U1.11 (D3)
unnamed: RN2.1 (R1.1), U1.10 (D4)
unnamed: RN2.2 (R2.1), U1.9 (D5)
unnamed: RN2.3 (R3.1), U1.8 (D6)
unnamed: RN2.4 (R4.1), U1.7 (D7)
unnamed: RN3.1 (R1.1), U1.6 (D8)
unnamed: RN3.2 (R2.1), U1.5 (D9)
unnamed: RN3.3 (R3.1), U1.4 (D10)
unnamed: RN3.4 (R4.1), U1.3 (D11)
unnamed: RN4.1 (R1.1), U1.2 (D12)
unnamed: RN4.2 (R2.1), U1.1 (D13)
unnamed: R3.1, U1.28 (CLK)
unnamed: R6.2, RV1.1, U1.18 (FS_ADJ)
unnamed: R7.2, R9.1, U1.22 (IOUTA)
unnamed: R8.1, R10.1, U1.21 (IOUTB)
unnamed: R5.1, U1.25 (MODE)
unnamed: C7.1, U1.17 (REFIO)
unnamed: R4.2, U1.16 (REFLO)
unnamed: R10.2, R11.1, R12.1, U2.3 (+)
unnamed: R9.2, R13.1, U2.2 (-)
unnamed: R2.2, R3.2, X1.3 (OUT)
unnamed: R1.2, X1.1 (~ST)
VDD: C5.1, C6.1, C8.1, FB2.2, R12.2, U1.24 (AVDD), U2.7 (V+)

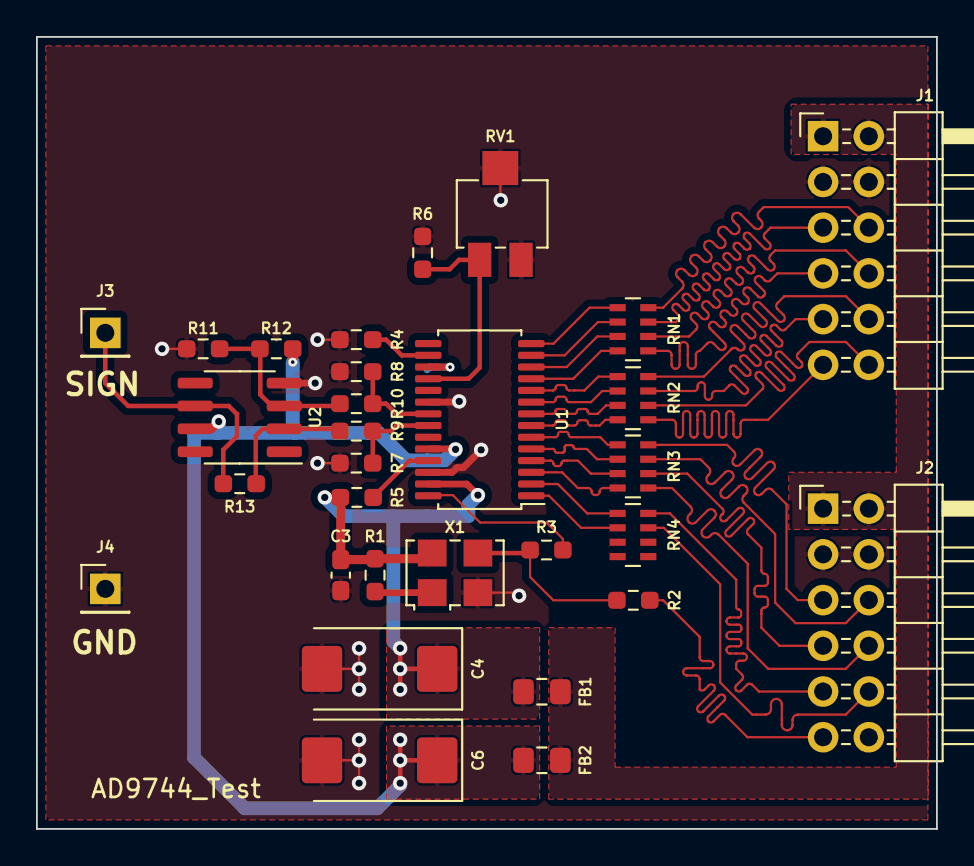
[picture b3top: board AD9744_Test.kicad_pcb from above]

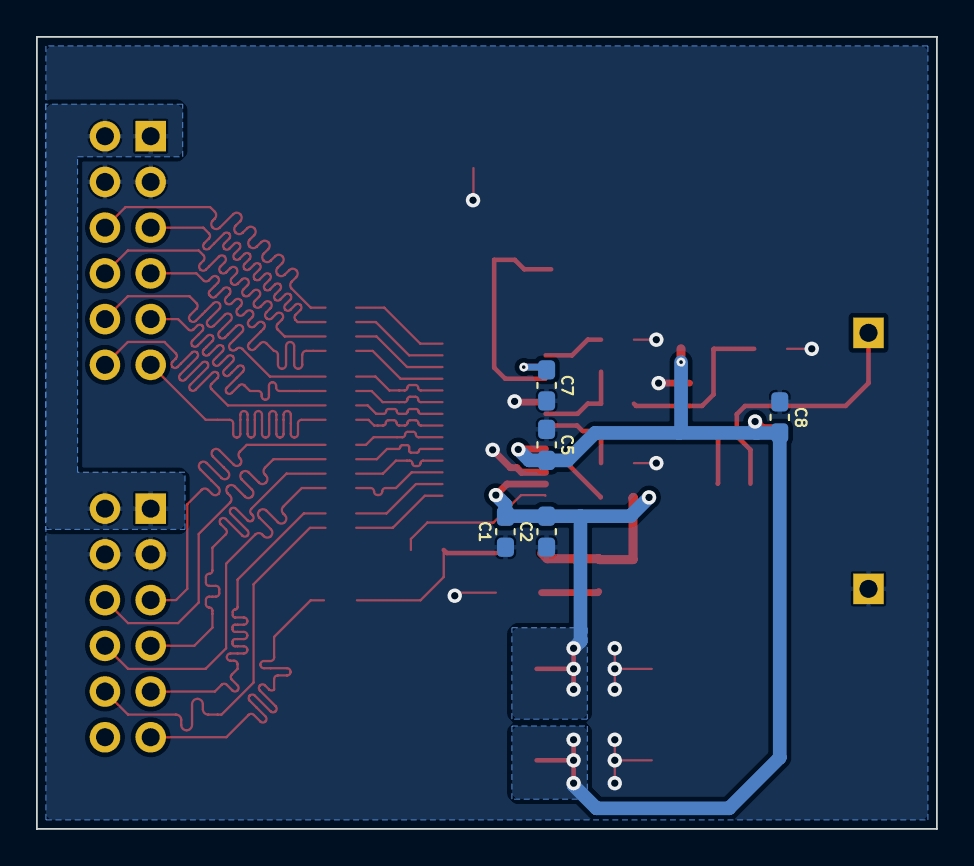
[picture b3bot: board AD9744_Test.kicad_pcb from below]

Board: 2 copper layers, 50.0 x 44.0 mm, 35 parts (5 on the bottom side), 45 nets.

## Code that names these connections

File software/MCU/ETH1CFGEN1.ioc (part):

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Mcu.Name=STM32H723ZGTx
Mcu.Package=LQFP144
Mcu.UserName=STM32H723ZGTx
PA1.GPIOParameters=GPIO_Speed,GPIO_Label
PA1.GPIO_Label=RMII_REF_CLK
PA1.GPIO_Speed=GPIO_SPEED_FREQ_VERY_HIGH
PA1.Mode=RMII
PA1.Signal=ETH_REF_CLK
PA10.GPIOParameters=GPIO_Label
PA10.GPIO_Label=TRIG_EN
PA10.Signal=GPIO_Output
PA13(JTMS/SWDIO).GPIOParameters=GPIO_Label
PA13(JTMS/SWDIO).GPIO_Label=SWDIO
PA13(JTMS/SWDIO).Mode=Trace_Asynchronous_SW
PA13(JTMS/SWDIO).Signal=DEBUG_JTMS-SWDIO
PA14(JTCK/SWCLK).GPIOParameters=GPIO_Label
PA14(JTCK/SWCLK).GPIO_Label=SWCLK
PA14(JTCK/SWCLK).Mode=Trace_Asynchronous_SW
PA14(JTCK/SWCLK).Signal=DEBUG_JTCK-SWCLK
PA2.GPIOParameters=GPIO_Speed,GPIO_Label
PA2.GPIO_Label=RMII_MDIO
PA2.GPIO_Speed=GPIO_SPEED_FREQ_VERY_HIGH
PA2.Mode=RMII
PA2.Signal=ETH_MDIO
PA7.GPIOParameters=GPIO_Speed,GPIO_Label
PA7.GPIO_Label=RMII_CRS_DV
PA7.GPIO_Speed=GPIO_SPEED_FREQ_VERY_HIGH
PA7.Mode=RMII
PA7.Signal=ETH_CRS_DV
PA8.GPIOParameters=GPIO_Label
PA8.GPIO_Label=TRIG_IN
PA8.Signal=GPIO_Input
PA9.GPIOParameters=GPIO_Label
PA9.GPIO_Label=TRIG_OUT
PA9.Signal=GPIO_Output
PB13.GPIOParameters=GPIO_Speed,GPIO_Label
PB13.GPIO_Label=RMII_TXD1
PB13.GPIO_Speed=GPIO_SPEED_FREQ_VERY_HIGH
PB13.Mode=RMII
PB13.Signal=ETH_TXD1
PB3(JTDO/TRACESWO).GPIOParameters=GPIO_Label
PB3(JTDO/TRACESWO).GPIO_Label=SWO
PB3(JTDO/TRACESWO).Mode=Trace_Asynchronous_SW
PB3(JTDO/TRACESWO).Signal=DEBUG_JTDO-SWO
PB5.GPIOParameters=GPIO_Label
PB5.GPIO_Label=EEPROM_WP
PB5.Signal=GPIO_Output
PB6.Mode=I2C
PB6.Signal=I2C1_SCL
PB7.Mode=I2C
PB7.Signal=I2C1_SDA
PC1.GPIOParameters=GPIO_Label
PC1.GPIO_Label=RMII_MDC
PC1.Mode=RMII
PC1.Signal=ETH_MDC
PC10.Mode=Full_Duplex_Master
PC10.Signal=SPI3_SCK
PC11.Mode=Full_Duplex_Master
PC11.Signal=SPI3_MISO
PC12.Mode=Full_Duplex_Master
PC12.Signal=SPI3_MOSI
PC13.Signal=GPIO_Input
PC4.GPIOParameters=GPIO_Speed,GPIO_Label
PC4.GPIO_Label=RMII_RXD0
PC4.GPIO_Speed=GPIO_SPEED_FREQ_VERY_HIGH
PC4.Mode=RMII
PC4.Signal=ETH_RXD0
PC5.GPIOParameters=GPIO_Speed,GPIO_Label
PC5.GPIO_Label=RMII_RXD1
PC5.GPIO_Speed=GPIO_SPEED_FREQ_VERY_HIGH
PC5.Mode=RMII
PC5.Signal=ETH_RXD1
PD0.GPIOParameters=GPIO_Speed,PinState,GPIO_PuPd,GPIO_Label
PD0.GPIO_Label=SPI3_NSS
PD0.GPIO_PuPd=GPIO_PULLDOWN
PD0.GPIO_Speed=GPIO_SPEED_FREQ_VERY_HIGH
PD0.PinState=GPIO_PIN_SET
PD0.Signal=GPIO_Output
PD11.GPIOParameters=GPIO_Label
PD11.GPIO_Label=TRIG_IN
PD11.Signal=GPIO_Input
PD12.GPIOParameters=GPIO_Label
PD12.GPIO_Label=TRIG_OUT
PD12.Signal=GPIO_Output
PD13.GPIOParameters=GPIO_Label
PD13.GPIO_Label=TRIG_EN
PD13.Signal=GPIO_Output
PD14.GPIOParameters=GPIO_Label
PD14.GPIO_Label=CXN_REL6
PD14.Signal=GPIO_Output
PD15.GPIOParameters=GPIO_Label
PD15.GPIO_Label=CXN_REL5
PD15.Signal=GPIO_Output
PD3.GPIOParameters=GPIO_Speed,PinState,GPIO_Label
PD3.GPIO_Label=MCU_GPIO1
PD3.GPIO_Speed=GPIO_SPEED_FREQ_HIGH
PD3.PinState=GPIO_PIN_SET
PD3.Signal=GPIO_Output
PD4.GPIOParameters=GPIO_Label
PD4.GPIO_Label=MCU_GPIO2
PD4.Signal=GPIO_Input
PE13.GPIOParameters=GPIO_Label
PE13.GPIO_Label=MCU_DEFAULT
PE13.Signal=GPIO_Input
PF0.Mode=I2C
PF0.Signal=I2C2_SDA
PF1.Mode=I2C
PF1.Signal=I2C2_SCL
PF3.GPIOParameters=GPIO_Label
PF3.GPIO_Label=LED_GREEN
PF3.Signal=GPIO_Output
PF4.GPIOParameters=GPIO_Label
PF4.GPIO_Label=LED_RED
PF4.Signal=GPIO_Output
PF5.GPIOParameters=GPIO_Label
PF5.GPIO_Label=LED_BLUE
PF5.Signal=GPIO_Output
PG11.GPIOParameters=GPIO_Speed,GPIO_Label
PG11.GPIO_Label=RMII_TX_EN
PG11.GPIO_Speed=GPIO_SPEED_FREQ_VERY_HIGH
PG11.Mode=RMII
PG11.Signal=ETH_TX_EN
PG13.GPIOParameters=GPIO_Speed,GPIO_Label
PG13.GPIO_Label=RMII_TXD0
PG13.GPIO_Speed=GPIO_SPEED_FREQ_VERY_HIGH
PG13.Mode=RMII
PG13.Signal=ETH_TXD0
PG2.GPIOParameters=GPIO_Label
PG2.GPIO_Label=CXN_REL4
PG2.Signal=GPIO_Output
PG3.GPIOParameters=GPIO_Label
PG3.GPIO_Label=CXN_REL3
PG3.Signal=GPIO_Output
PG4.GPIOParameters=GPIO_Label
PG4.GPIO_Label=CXN_REL2
PG4.Signal=GPIO_Output
PG5.GPIOParameters=GPIO_Label
PG5.GPIO_Label=CXN_REL1
PG5.Signal=GPIO_Output
PH0-OSC_IN.GPIOParameters=GPIO_Label
PH0-OSC_IN.GPIO_Label=MCO
PH0-OSC_IN.Mode=HSE-External-Clock-Source
PH0-OSC_IN.Signal=RCC_OSC_IN
RCC.HSE_VALUE=8000000
RCC.SYSCLKFreq_VALUE=500000000
RCC.SYSCLKSource=RCC_SYSCLKSOURCE_PLLCLK
board=NUCLEO-H723ZG
boardIOC=true

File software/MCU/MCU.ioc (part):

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Mcu.Name=STM32H723ZGTx
Mcu.Package=LQFP144
Mcu.UserName=STM32H723ZGTx
PA1.GPIOParameters=GPIO_Speed,GPIO_Label
PA1.GPIO_Label=RMII_REF_CLK
PA1.GPIO_Speed=GPIO_SPEED_FREQ_VERY_HIGH
PA1.Mode=RMII
PA1.Signal=ETH_REF_CLK
PA13(JTMS/SWDIO).GPIOParameters=GPIO_Label
PA13(JTMS/SWDIO).GPIO_Label=SWDIO
PA13(JTMS/SWDIO).Mode=Trace_Asynchronous_SW
PA13(JTMS/SWDIO).Signal=DEBUG_JTMS-SWDIO
PA14(JTCK/SWCLK).GPIOParameters=GPIO_Label
PA14(JTCK/SWCLK).GPIO_Label=SWCLK
PA14(JTCK/SWCLK).Mode=Trace_Asynchronous_SW
PA14(JTCK/SWCLK).Signal=DEBUG_JTCK-SWCLK
PA2.GPIOParameters=GPIO_Speed,GPIO_Label
PA2.GPIO_Label=RMII_MDIO
PA2.GPIO_Speed=GPIO_SPEED_FREQ_VERY_HIGH
PA2.Mode=RMII
PA2.Signal=ETH_MDIO
PA4.GPIOParameters=GPIO_Speed
PA4.GPIO_Speed=GPIO_SPEED_FREQ_VERY_HIGH
PA4.Mode=PSSI_8
PA4.Signal=PSSI_DE
PA5.GPIOParameters=GPIO_Speed,GPIO_PuPd
PA5.GPIO_PuPd=GPIO_PULLDOWN
PA5.GPIO_Speed=GPIO_SPEED_FREQ_HIGH
PA5.Mode=TX_Only_Simplex_Unidirect_Master
PA5.Signal=SPI1_SCK
PA6.GPIOParameters=GPIO_Speed,GPIO_PuPd
PA6.GPIO_PuPd=GPIO_PULLDOWN
PA6.GPIO_Speed=GPIO_SPEED_FREQ_VERY_HIGH
PA6.Mode=PSSI_8
PA6.Signal=PSSI_PDCK
PA7.GPIOParameters=GPIO_Speed,GPIO_Label
PA7.GPIO_Label=RMII_CRS_DV
PA7.GPIO_Speed=GPIO_SPEED_FREQ_VERY_HIGH
PA7.Mode=RMII
PA7.Signal=ETH_CRS_DV
PB0.GPIOParameters=GPIO_Label
PB0.GPIO_Label=LED_GREEN
PB0.Signal=GPIO_Output
PB10.GPIOParameters=GPIO_Speed,PinState,GPIO_Label
PB10.GPIO_Label=SPI1_SSEL
PB10.GPIO_Speed=GPIO_SPEED_FREQ_HIGH
PB10.PinState=GPIO_PIN_SET
PB10.Signal=GPIO_Output
PB13.GPIOParameters=GPIO_Speed,GPIO_Label
PB13.GPIO_Label=RMII_TXD1
PB13.GPIO_Speed=GPIO_SPEED_FREQ_VERY_HIGH
PB13.Mode=RMII
PB13.Signal=ETH_TXD1
PB14.GPIOParameters=GPIO_Label
PB14.GPIO_Label=LED_RED
PB14.Signal=GPIO_Output
PB3(JTDO/TRACESWO).GPIOParameters=GPIO_Label
PB3(JTDO/TRACESWO).GPIO_Label=SWO
PB3(JTDO/TRACESWO).Mode=Trace_Asynchronous_SW
PB3(JTDO/TRACESWO).Signal=DEBUG_JTDO-SWO
PB5.GPIOParameters=GPIO_Speed,GPIO_PuPd
PB5.GPIO_PuPd=GPIO_PULLDOWN
PB5.GPIO_Speed=GPIO_SPEED_FREQ_HIGH
PB5.Mode=TX_Only_Simplex_Unidirect_Master
PB5.Signal=SPI1_MOSI
PC1.GPIOParameters=GPIO_Label
PC1.GPIO_Label=RMII_MDC
PC1.Mode=RMII
PC1.Signal=ETH_MDC
PC11.GPIOParameters=GPIO_Speed
PC11.GPIO_Speed=GPIO_SPEED_FREQ_VERY_HIGH
PC11.Mode=PSSI_8
PC11.Signal=PSSI_D4
PC13.GPIOParameters=GPIO_Label
PC13.GPIO_Label=B1_Blue
PC13.Signal=GPIO_Input
PC4.GPIOParameters=GPIO_Speed,GPIO_Label
PC4.GPIO_Label=RMII_RXD0
PC4.GPIO_Speed=GPIO_SPEED_FREQ_VERY_HIGH
PC4.Mode=RMII
PC4.Signal=ETH_RXD0
PC5.GPIOParameters=GPIO_Speed,GPIO_Label
PC5.GPIO_Label=RMII_RXD1
PC5.GPIO_Speed=GPIO_SPEED_FREQ_VERY_HIGH
PC5.Mode=RMII
PC5.Signal=ETH_RXD1
PC6.GPIOParameters=GPIO_Speed
PC6.GPIO_Speed=GPIO_SPEED_FREQ_VERY_HIGH
PC6.Mode=PSSI_8
PC6.Signal=PSSI_D0
PC7.GPIOParameters=GPIO_Speed
PC7.GPIO_Speed=GPIO_SPEED_FREQ_VERY_HIGH
PC7.Mode=PSSI_8
PC7.Signal=PSSI_D1
PC8.GPIOParameters=GPIO_Speed
PC8.GPIO_Speed=GPIO_SPEED_FREQ_VERY_HIGH
PC8.Mode=PSSI_8
PC8.Signal=PSSI_D2
PC9.GPIOParameters=GPIO_Speed
PC9.GPIO_Speed=GPIO_SPEED_FREQ_VERY_HIGH
PC9.Mode=PSSI_8
PC9.Signal=PSSI_D3
PD10.GPIOParameters=GPIO_Label
PD10.GPIO_Label=USB_FS_PWR_EN
PD10.Signal=GPIO_Output
PD3.GPIOParameters=GPIO_Speed
PD3.GPIO_Speed=GPIO_SPEED_FREQ_VERY_HIGH
PD3.Mode=PSSI_8
PD3.Signal=PSSI_D5
PE1.GPIOParameters=GPIO_Label
PE1.GPIO_Label=LED_YELLOW
PE1.Signal=GPIO_Output
PE5.GPIOParameters=GPIO_Speed
PE5.GPIO_Speed=GPIO_SPEED_FREQ_VERY_HIGH
PE5.Mode=PSSI_8
PE5.Signal=PSSI_D6
PE6.GPIOParameters=GPIO_Speed
PE6.GPIO_Speed=GPIO_SPEED_FREQ_VERY_HIGH
PE6.Mode=PSSI_8
PE6.Signal=PSSI_D7
PG11.GPIOParameters=GPIO_Speed,GPIO_Label
PG11.GPIO_Label=RMII_TX_EN
PG11.GPIO_Speed=GPIO_SPEED_FREQ_VERY_HIGH
PG11.Mode=RMII
PG11.Signal=ETH_TX_EN
PG13.GPIOParameters=GPIO_Speed,GPIO_Label
PG13.GPIO_Label=RMII_TXD0
PG13.GPIO_Speed=GPIO_SPEED_FREQ_VERY_HIGH
PG13.Mode=RMII
PG13.Signal=ETH_TXD0
PG7.GPIOParameters=GPIO_Label
PG7.GPIO_Label=USB_FS_OVCR
PG7.Signal=GPXTI7
PG9.GPIOParameters=GPIO_Speed
PG9.GPIO_Speed=GPIO_SPEED_FREQ_VERY_HIGH
PG9.Mode=PSSI_8
PG9.Signal=PSSI_RDY
PH0-OSC_IN.GPIOParameters=GPIO_Label
PH0-OSC_IN.GPIO_Label=MCO
PH0-OSC_IN.Mode=HSE-External-Clock-Source
PH0-OSC_IN.Signal=RCC_OSC_IN
RCC.HSE_VALUE=8000000
RCC.SYSCLKFreq_VALUE=500000000
RCC.SYSCLKSource=RCC_SYSCLKSOURCE_PLLCLK
board=NUCLEO-H723ZG
boardIOC=true

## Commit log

2019-08-22 Schematic development
2023-08-03 Got STM32H723 Ethernet and SCPI to work. NOTE: Using NUCLEO board for software development.
2023-08-07 Development
2023-08-24 Hardware development
2023-09-24 FPGA code
2023-09-28 FPGA design
2023-10-03 FPGA tests
2023-10-06 Software and hardware changes
2023-12-03 PCB design
2023-12-26 Added SDRAM
2024-01-06 Schematic and PCB design
2024-01-11 FPGA : SPI slave test. The Lattice slave implementation works for MOSI, MISO doesn't.
2024-01-18 Software development
2024-01-18 Added files
